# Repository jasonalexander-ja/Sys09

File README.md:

# Sys09 

Contains respositories for code and schematics/PCB layouts for the Sys09 6809 based computer.

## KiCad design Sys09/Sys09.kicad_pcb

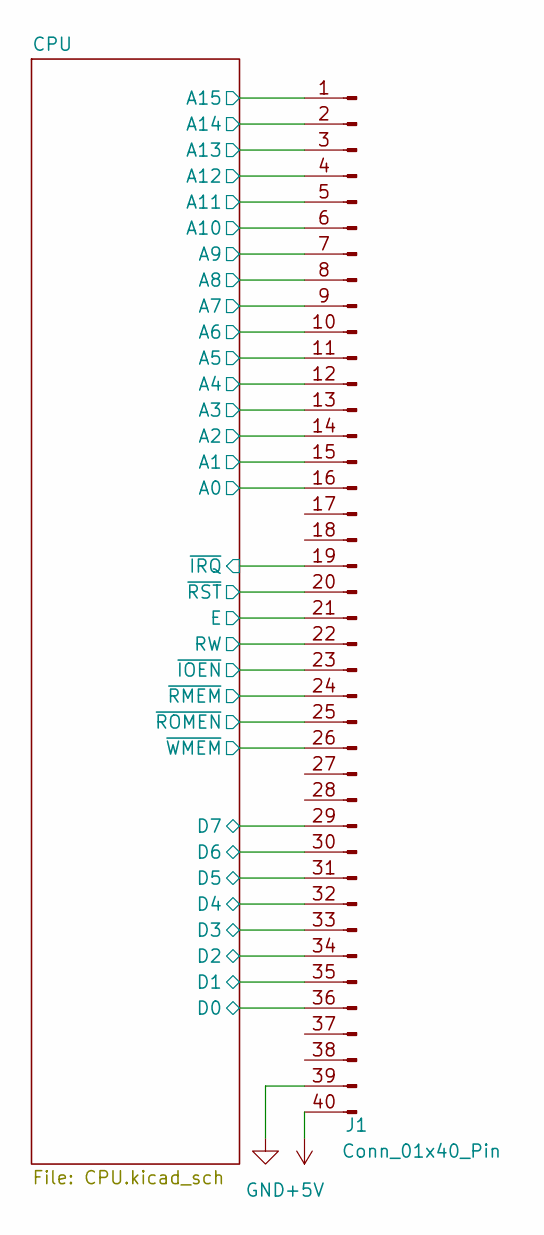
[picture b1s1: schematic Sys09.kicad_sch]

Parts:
J1: Conn_01x40_Pin; PinHeader_1x40_P2.54mm_Vertical

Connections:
+5V: J1.40; also elsewhere on the board
/CPU/A0: J1.16; also elsewhere on the board
/CPU/A1: J1.15; also elsewhere on the board
/CPU/A2: J1.14; also elsewhere on the board
/CPU/A3: J1.13; also elsewhere on the board
/CPU/A4: J1.12; also elsewhere on the board
/CPU/A5: J1.11; also elsewhere on the board
/CPU/A6: J1.10; also elsewhere on the board
/CPU/A7: J1.9; also elsewhere on the board
/CPU/A8: J1.8; also elsewhere on the board
/CPU/A9: J1.7; also elsewhere on the board
/CPU/A10: J1.6; also elsewhere on the board
/CPU/A11: J1.5; also elsewhere on the board
/CPU/A12: J1.4; also elsewhere on the board
/CPU/A13: J1.3; also elsewhere on the board
/CPU/A14: J1.2; also elsewhere on the board
/CPU/A15: J1.1; also elsewhere on the board
/CPU/D0: J1.36; also elsewhere on the board
/CPU/D1: J1.35; also elsewhere on the board
/CPU/D2: J1.34; also elsewhere on the board
/CPU/D3: J1.33; also elsewhere on the board
/CPU/D4: J1.32; also elsewhere on the board
/CPU/D5: J1.31; also elsewhere on the board
/CPU/D6: J1.30; also elsewhere on the board
/CPU/D7: J1.29; also elsewhere on the board
/CPU/E: J1.21; also elsewhere on the board
/CPU/RW: J1.22; also elsewhere on the board
/CPU/~IOEN: J1.23; also elsewhere on the board
/CPU/~IRQ: J1.19; also elsewhere on the board
/CPU/~RMEM: J1.24; also elsewhere on the board
/CPU/~ROMEN: J1.25; also elsewhere on the board
/CPU/~RST: J1.20; also elsewhere on the board
/CPU/~WMEM: J1.26; also elsewhere on the board
GND: J1.39; also elsewhere on the board

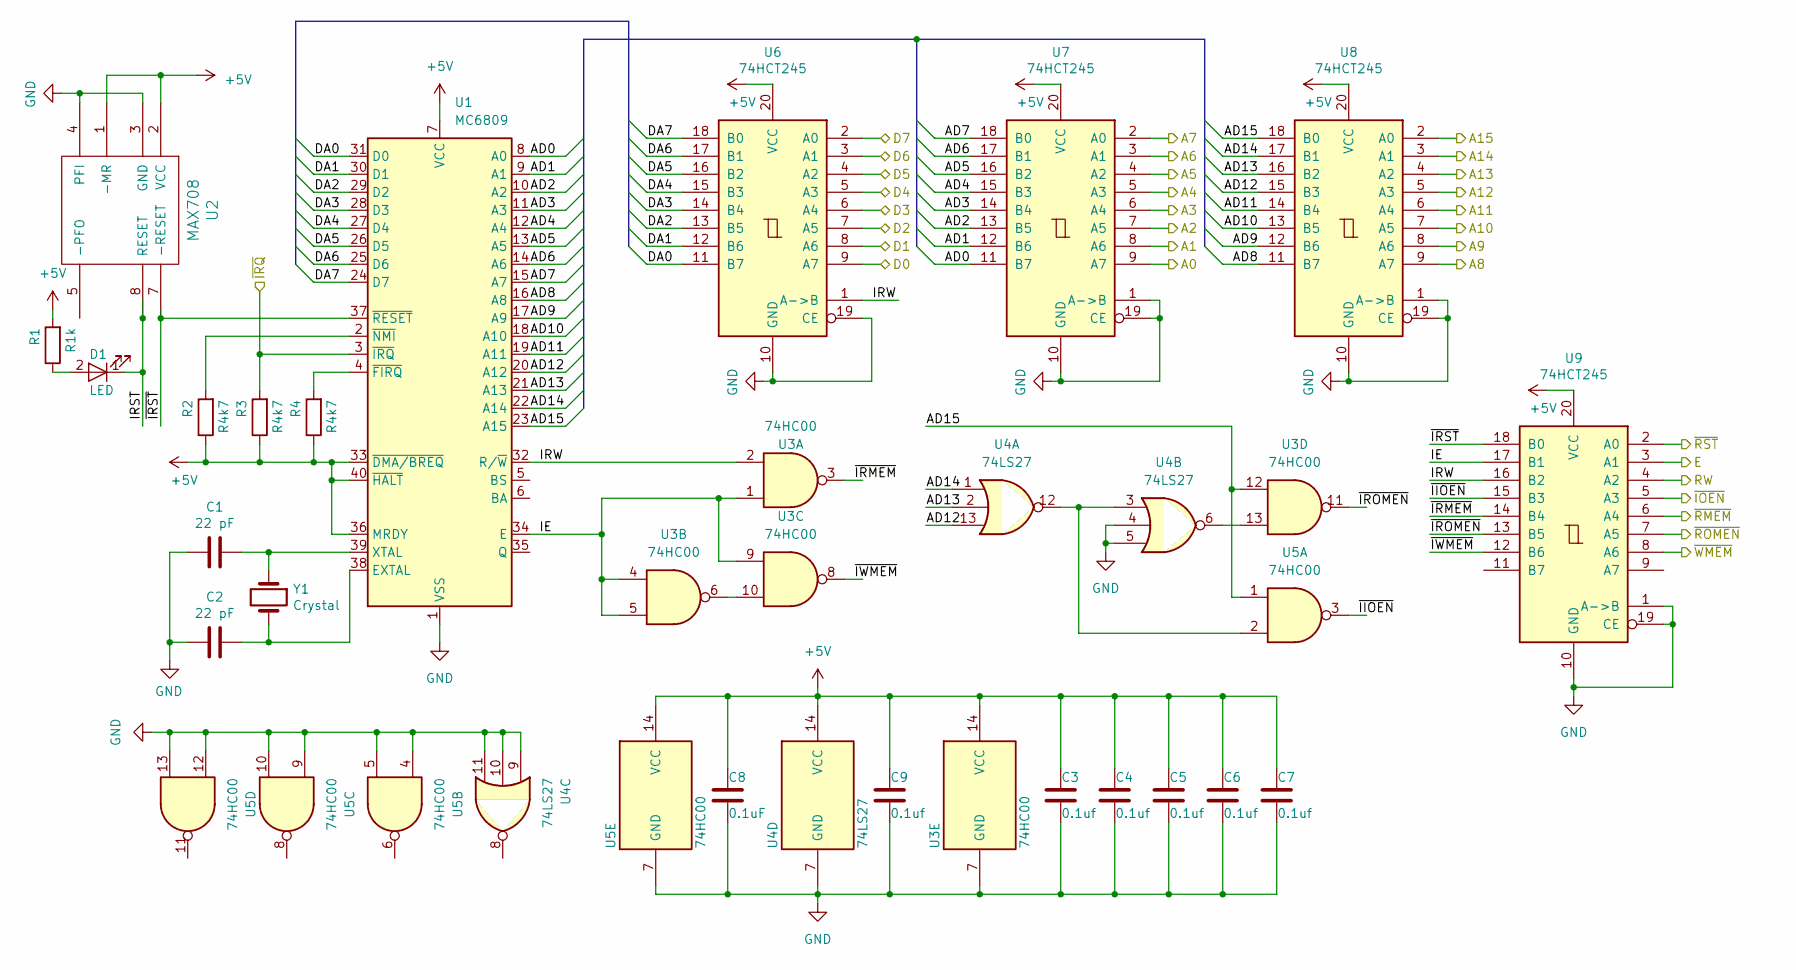
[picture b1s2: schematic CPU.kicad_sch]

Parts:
C1, C2: 22 pF; C_Disc_D5.0mm_W2.5mm_P2.50mm
C3, C4, C5, C6, C7, C9: 0.1uf; C_Disc_D5.0mm_W2.5mm_P2.50mm
C8: 0.1uF; C_Disc_D5.0mm_W2.5mm_P2.50mm
D1: LED; LED_D3.0mm
R1: R1k; R_Axial_DIN0207_L6.3mm_D2.5mm_P7.62mm_Horizontal
R2, R3, R4: R4k7; R_Axial_DIN0207_L6.3mm_D2.5mm_P7.62mm_Horizontal
U1: MC6809; DIP-40_W15.24mm
U2: MAX708; DIP-8_W7.62mm
U3, U5: 74HC00; DIP-14_W7.62mm
U4: 74LS27; DIP-14_W7.62mm
U6, U7, U8, U9: 74HCT245; DIP-20_W7.62mm
Y1: Crystal; Crystal_HC52-8mm_Vertical

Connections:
+5V: C3.1, C4.1, C5.1, C6.1, C7.1, C8.1, C9.1, R1.2, R2.1, R3.1, R4.1, U1.7 (VCC), U1.33 (~DMA/BREQ), U1.36 (MRDY), U1.40 (~HALT), U2.1 (-MR), U2.2 (VCC), U3.14 (VCC), U4.14 (VCC), U5.14 (VCC), U6.20 (VCC), U7.20 (VCC), U8.20 (VCC), U9.20 (VCC); also elsewhere on the board
/CPU/A0: U7.9 (A7); also elsewhere on the board
/CPU/A1: U7.8 (A6); also elsewhere on the board
/CPU/A2: U7.7 (A5); also elsewhere on the board
/CPU/A3: U7.6 (A4); also elsewhere on the board
/CPU/A4: U7.5 (A3); also elsewhere on the board
/CPU/A5: U7.4 (A2); also elsewhere on the board
/CPU/A6: U7.3 (A1); also elsewhere on the board
/CPU/A7: U7.2 (A0); also elsewhere on the board
/CPU/A8: U8.9 (A7); also elsewhere on the board
/CPU/A9: U8.8 (A6); also elsewhere on the board
/CPU/A10: U8.7 (A5); also elsewhere on the board
/CPU/A11: U8.6 (A4); also elsewhere on the board
/CPU/A12: U8.5 (A3); also elsewhere on the board
/CPU/A13: U8.4 (A2); also elsewhere on the board
/CPU/A14: U8.3 (A1); also elsewhere on the board
/CPU/A15: U8.2 (A0); also elsewhere on the board
/CPU/AD0: U1.8 (A0), U7.11 (B7)
/CPU/AD1: U1.9 (A1), U7.12 (B6)
/CPU/AD2: U1.10 (A2), U7.13 (B5)
/CPU/AD3: U1.11 (A3), U7.14 (B4)
/CPU/AD4: U1.12 (A4), U7.15 (B3)
/CPU/AD5: U1.13 (A5), U7.16 (B2)
/CPU/AD6: U1.14 (A6), U7.17 (B1)
/CPU/AD7: U1.15 (A7), U7.18 (B0)
/CPU/AD8: U1.16 (A8), U8.11 (B7)
/CPU/AD9: U1.17 (A9), U8.12 (B6)
/CPU/AD10: U1.18 (A10), U8.13 (B5)
/CPU/AD11: U1.19 (A11), U8.14 (B4)
/CPU/AD12: U1.20 (A12), U4.13, U8.15 (B3)
/CPU/AD13: U1.21 (A13), U4.2, U8.16 (B2)
/CPU/AD14: U1.22 (A14), U4.1, U8.17 (B1)
/CPU/AD15: U1.23 (A15), U3.12, U5.1, U8.18 (B0)
/CPU/D0: U6.9 (A7); also elsewhere on the board
/CPU/D1: U6.8 (A6); also elsewhere on the board
/CPU/D2: U6.7 (A5); also elsewhere on the board
/CPU/D3: U6.6 (A4); also elsewhere on the board
/CPU/D4: U6.5 (A3); also elsewhere on the board
/CPU/D5: U6.4 (A2); also elsewhere on the board
/CPU/D6: U6.3 (A1); also elsewhere on the board
/CPU/D7: U6.2 (A0); also elsewhere on the board
/CPU/DA0: U1.31 (D0), U6.11 (B7)
/CPU/DA1: U1.30 (D1), U6.12 (B6)
/CPU/DA2: U1.29 (D2), U6.13 (B5)
/CPU/DA3: U1.28 (D3), U6.14 (B4)
/CPU/DA4: U1.27 (D4), U6.15 (B3)
/CPU/DA5: U1.26 (D5), U6.16 (B2)
/CPU/DA6: U1.25 (D6), U6.17 (B1)
/CPU/DA7: U1.24 (D7), U6.18 (B0)
/CPU/E: U9.3 (A1); also elsewhere on the board
/CPU/IE: U1.34 (E), U3.1, U3.4, U3.5, U3.9, U9.17 (B1)
/CPU/IRST: D1.1 (K), U2.8 (RESET)
/CPU/IRW: U1.32 (R/~W), U3.2, U6.1 (A->B), U9.16 (B2)
/CPU/RW: U9.4 (A2); also elsewhere on the board
/CPU/~IIOEN: U5.3, U9.15 (B3)
/CPU/~IOEN: U9.5 (A3); also elsewhere on the board
/CPU/~IRMEM: U3.3, U9.14 (B4)
/CPU/~IROMEN: U3.11, U9.13 (B5)
/CPU/~IRQ: R3.2, U1.3 (~IRQ); also elsewhere on the board
/CPU/~IRST: U1.37 (~RESET), U2.7 (-RESET), U9.18 (B0)
/CPU/~IWMEM: U3.8, U9.12 (B6)
/CPU/~RMEM: U9.6 (A4); also elsewhere on the board
/CPU/~ROMEN: U9.7 (A5); also elsewhere on the board
/CPU/~RST: U9.2 (A0); also elsewhere on the board
/CPU/~WMEM: U9.8 (A6); also elsewhere on the board
GND: C1.1, C2.1, C3.2, C4.2, C5.2, C6.2, C7.2, C8.2, C9.2, U1.1 (VSS), U2.3 (GND), U2.4 (PFI), U3.7 (GND), U4.4, U4.5, U4.7 (GND), U4.9, U4.10, U4.11, U5.4, U5.5, U5.7 (GND), U5.9, U5.10, U5.12, U5.13, U6.10 (GND), U6.19 (CE), U7.1 (A->B), U7.10 (GND), U7.19 (CE), U8.1 (A->B), U8.10 (GND), U8.19 (CE), U9.1 (A->B), U9.10 (GND), U9.19 (CE); also elsewhere on the board
unnamed: D1.2 (A), R1.1
unnamed: C2.2, U1.38 (EXTAL), Y1.2
unnamed: C1.2, U1.39 (XTAL), Y1.1
unnamed: R4.2, U1.4 (~FIRQ)
unnamed: R2.2, U1.2 (~NMI)
unnamed: U3.6, U3.10
unnamed: U3.13, U4.6
unnamed: U4.3, U4.12, U5.2

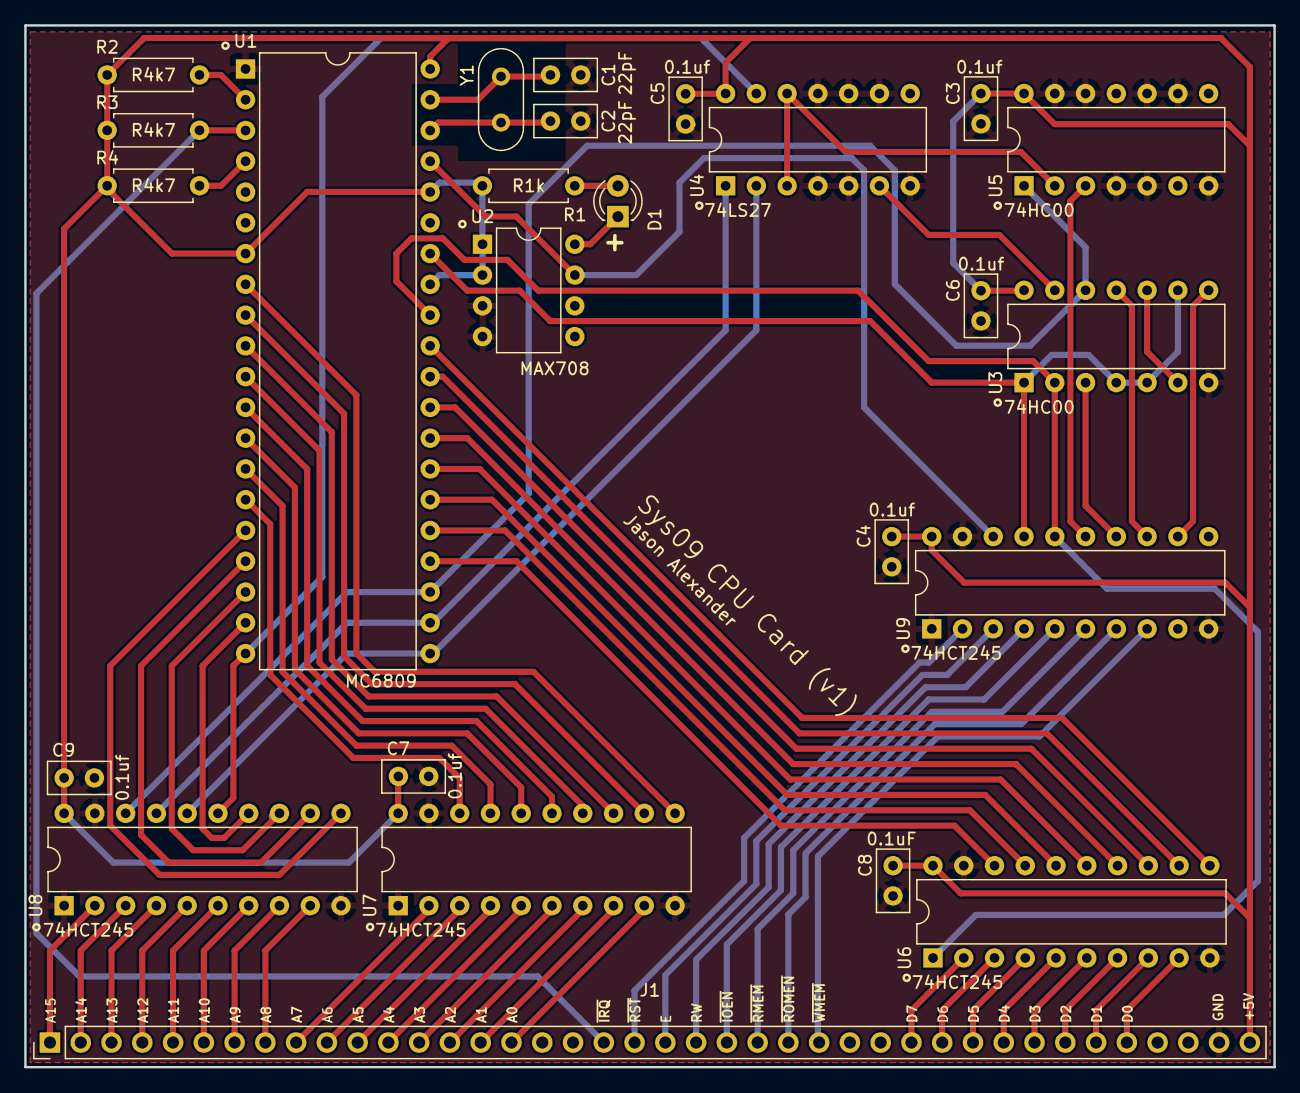
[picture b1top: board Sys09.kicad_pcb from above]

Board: 2 copper layers, 103.1 x 86.0 mm, 25 parts (0 on the bottom side), 74 nets.

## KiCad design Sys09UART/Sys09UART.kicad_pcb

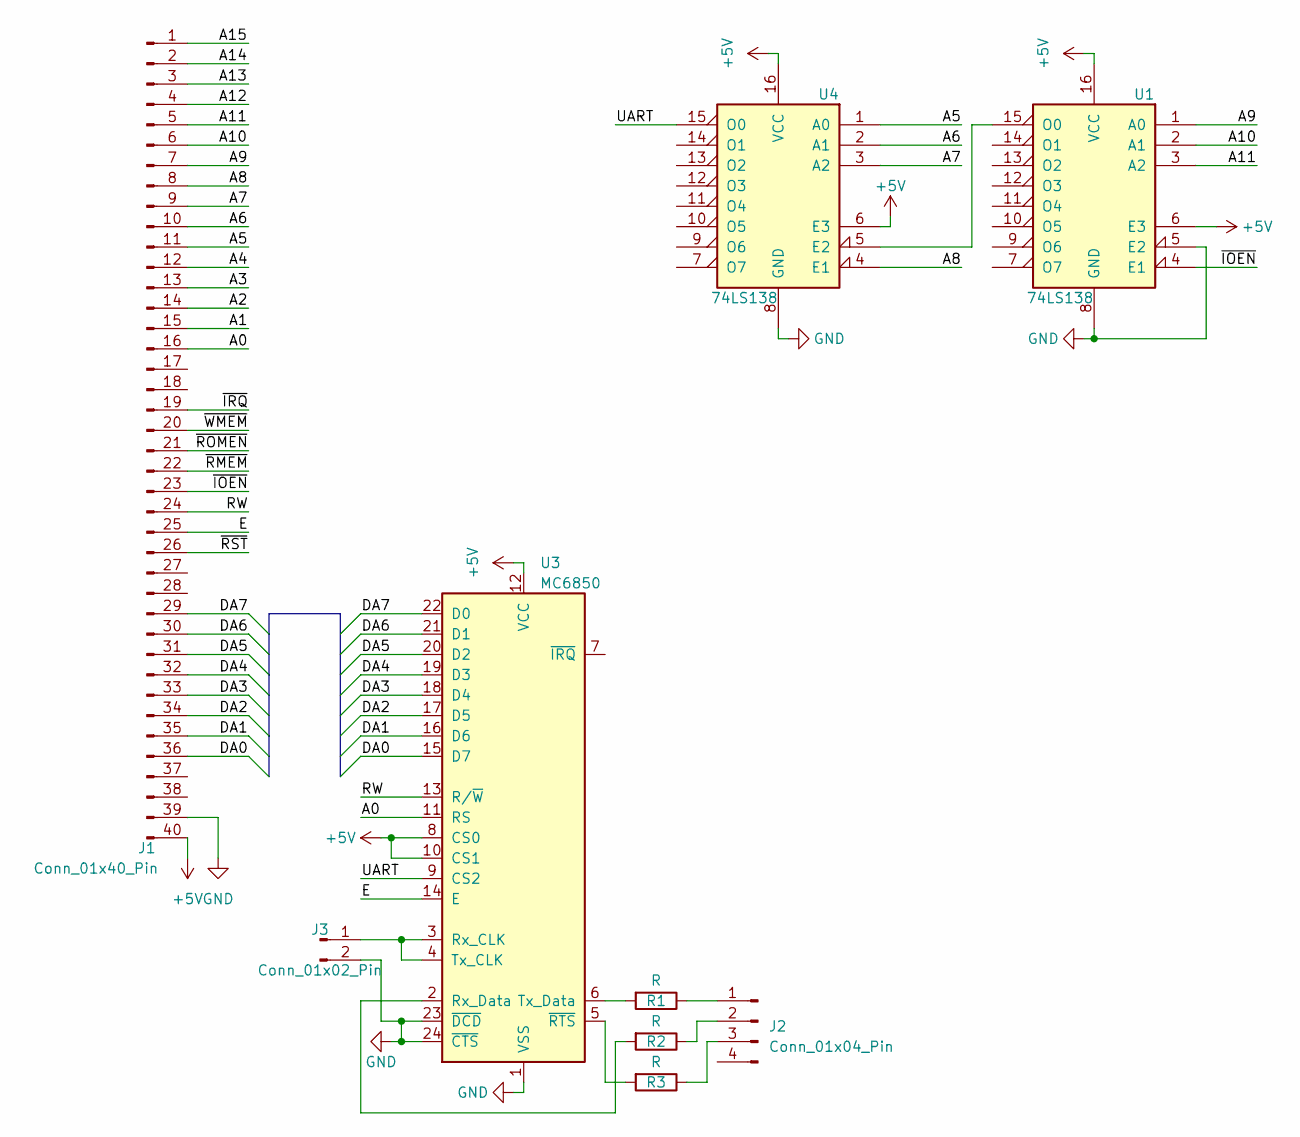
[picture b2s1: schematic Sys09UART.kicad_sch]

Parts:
J1: Conn_01x40_Pin; PinHeader_1x40_P2.54mm_Vertical
J2: Conn_01x04_Pin; PinHeader_1x04_P2.54mm_Vertical
J3: Conn_01x02_Pin; PinHeader_1x02_P2.54mm_Vertical
R1, R2, R3: R; R_Axial_DIN0207_L6.3mm_D2.5mm_P7.62mm_Horizontal
U1, U4: 74LS138; DIP-16_W7.62mm
U3: MC6850; DIP-24_W15.24mm

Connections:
+5V: J1.40, U1.6 (E3), U1.16 (VCC), U3.8 (CS0), U3.10 (CS1), U3.12 (VCC), U4.6 (E3), U4.16 (VCC)
/A0: J1.16, U3.11 (RS)
/A1: J1.15
/A2: J1.14
/A3: J1.13
/A4: J1.12
/A5: J1.11, U4.1 (A0)
/A6: J1.10, U4.2 (A1)
/A7: J1.9, U4.3 (A2)
/A8: J1.8, U4.4 (E1)
/A9: J1.7, U1.1 (A0)
/A10: J1.6, U1.2 (A1)
/A11: J1.5, U1.3 (A2)
/A12: J1.4
/A13: J1.3
/A14: J1.2
/A15: J1.1
/DA0: J1.36, U3.15 (D7)
/DA1: J1.35, U3.16 (D6)
/DA2: J1.34, U3.17 (D5)
/DA3: J1.33, U3.18 (D4)
/DA4: J1.32, U3.19 (D3)
/DA5: J1.31, U3.20 (D2)
/DA6: J1.30, U3.21 (D1)
/DA7: J1.29, U3.22 (D0)
/E: J1.25, U3.14 (E)
/RW: J1.24, U3.13 (R/~W)
/UART: U3.9 (CS2), U4.15 (O0)
/~IOEN: J1.23, U1.4 (E1)
/~IRQ: J1.19
/~RMEM: J1.22
/~ROMEN: J1.21
/~RST: J1.26
/~WMEM: J1.20
GND: J1.39, J3.2, U1.5 (E2), U1.8 (GND), U3.1 (VSS), U3.23 (~DCD), U3.24 (~CTS), U4.8 (GND)
unnamed: J2.1, R1.1
unnamed: J2.2, R2.1
unnamed: J2.3, R3.1
unnamed: J3.1, U3.3 (Rx_CLK), U3.4 (Tx_CLK)
unnamed: U1.15 (O0), U4.5 (E2)
unnamed: R2.2, U3.2 (Rx_Data)
unnamed: R1.2, U3.6 (Tx_Data)
unnamed: R3.2, U3.5 (~RTS)

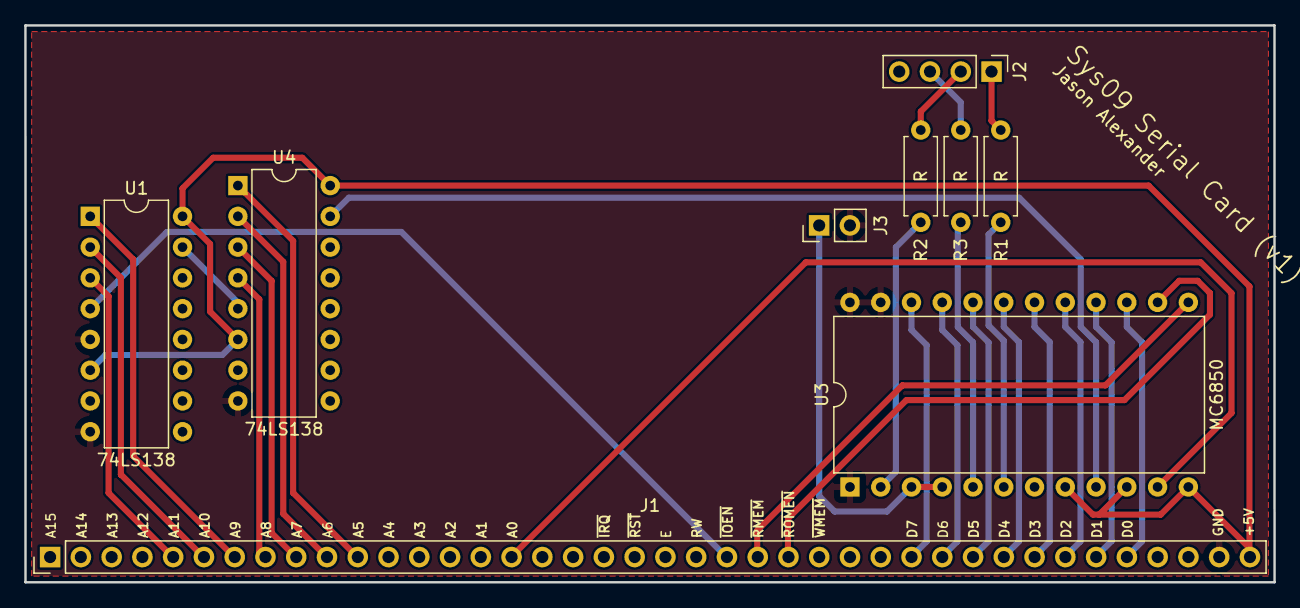
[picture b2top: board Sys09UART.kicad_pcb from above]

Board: 2 copper layers, 103.1 x 46.0 mm, 9 parts (0 on the bottom side), 30 nets.

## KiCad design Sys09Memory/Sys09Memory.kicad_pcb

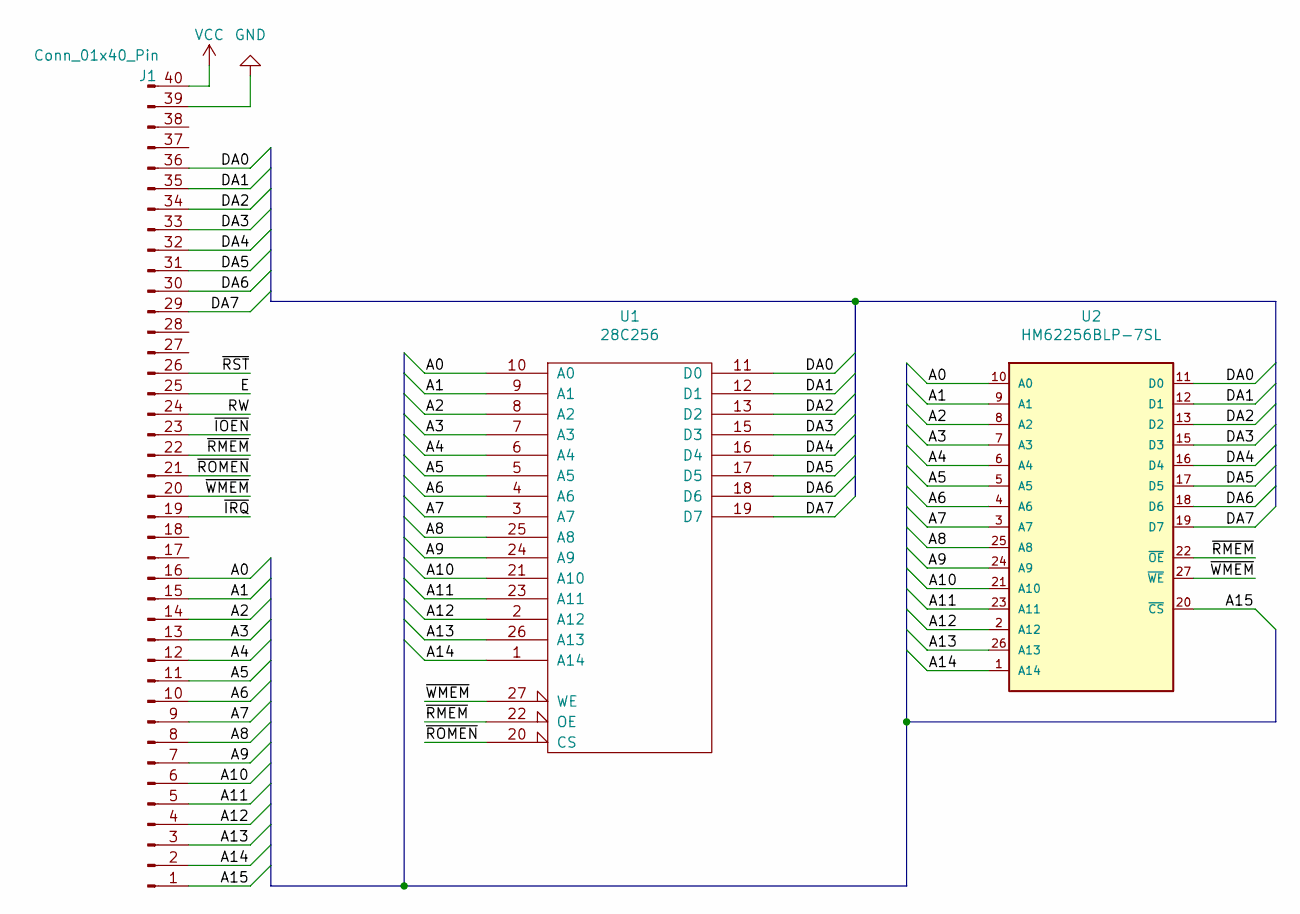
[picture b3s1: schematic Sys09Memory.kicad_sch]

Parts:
J1: Conn_01x40_Pin; PinHeader_1x40_P2.54mm_Vertical
U1: 28C256; DIP-28_W15.24mm
U2: HM62256BLP-7SL; DIP-28_W15.24mm

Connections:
/A0: J1.16, U1.10 (A0), U2.10 (A0)
/A1: J1.15, U1.9 (A1), U2.9 (A1)
/A2: J1.14, U1.8 (A2), U2.8 (A2)
/A3: J1.13, U1.7 (A3), U2.7 (A3)
/A4: J1.12, U1.6 (A4), U2.6 (A4)
/A5: J1.11, U1.5 (A5), U2.5 (A5)
/A6: J1.10, U1.4 (A6), U2.4 (A6)
/A7: J1.9, U1.3 (A7), U2.3 (A7)
/A8: J1.8, U1.25 (A8), U2.25 (A8)
/A9: J1.7, U1.24 (A9), U2.24 (A9)
/A10: J1.6, U1.21 (A10), U2.21 (A10)
/A11: J1.5, U1.23 (A11), U2.23 (A11)
/A12: J1.4, U1.2 (A12), U2.2 (A12)
/A13: J1.3, U1.26 (A13), U2.26 (A13)
/A14: J1.2, U1.1 (A14), U2.1 (A14)
/A15: J1.1, U2.20 (~CS)
/DA0: J1.36, U1.11 (D0), U2.11 (D0)
/DA1: J1.35, U1.12 (D1), U2.12 (D1)
/DA2: J1.34, U1.13 (D2), U2.13 (D2)
/DA3: J1.33, U1.15 (D3), U2.15 (D3)
/DA4: J1.32, U1.16 (D4), U2.16 (D4)
/DA5: J1.31, U1.17 (D5), U2.17 (D5)
/DA6: J1.30, U1.18 (D6), U2.18 (D6)
/DA7: J1.29, U1.19 (D7), U2.19 (D7)
/E: J1.25
/RW: J1.24
/~IOEN: J1.23
/~IRQ: J1.19
/~RMEM: J1.22, U1.22 (OE), U2.22 (~OE)
/~ROMEN: J1.21, U1.20 (CS)
/~RST: J1.26
/~WMEM: J1.20, U1.27 (WE), U2.27 (~WE)
GND: J1.39, U1.14 (GND), U2.14 (GND)
VCC: J1.40, U1.28 (VCC), U2.28 (VCC)

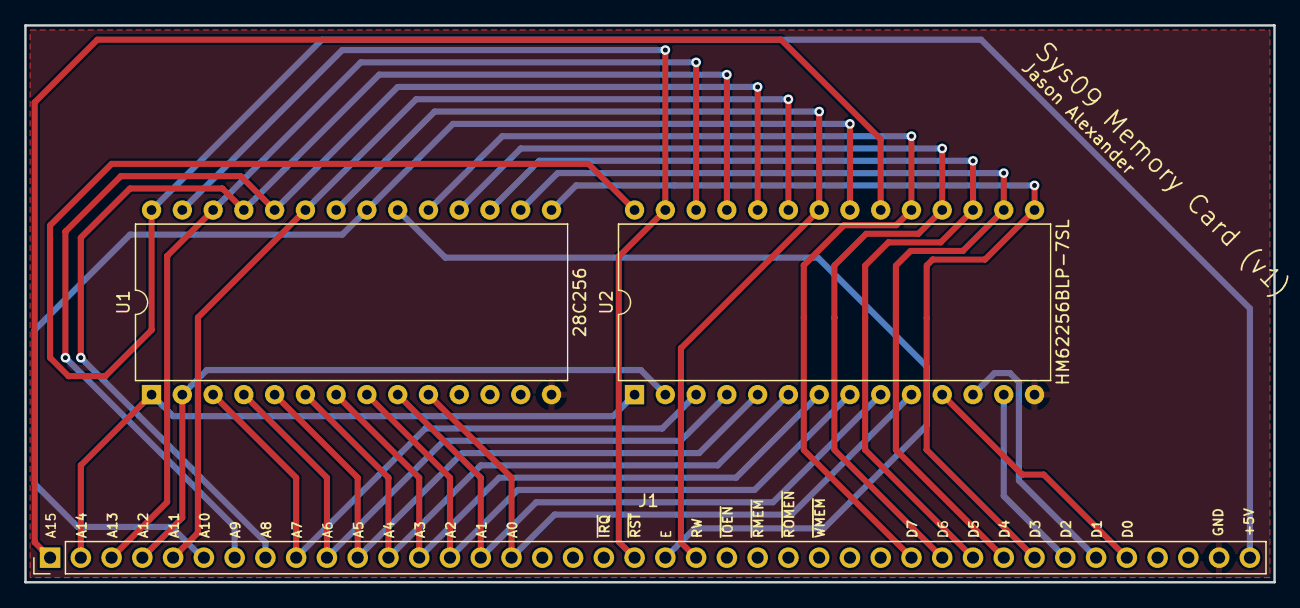
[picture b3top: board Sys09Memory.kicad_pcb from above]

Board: 2 copper layers, 103.1 x 46.0 mm, 3 parts (0 on the bottom side), 29 nets.

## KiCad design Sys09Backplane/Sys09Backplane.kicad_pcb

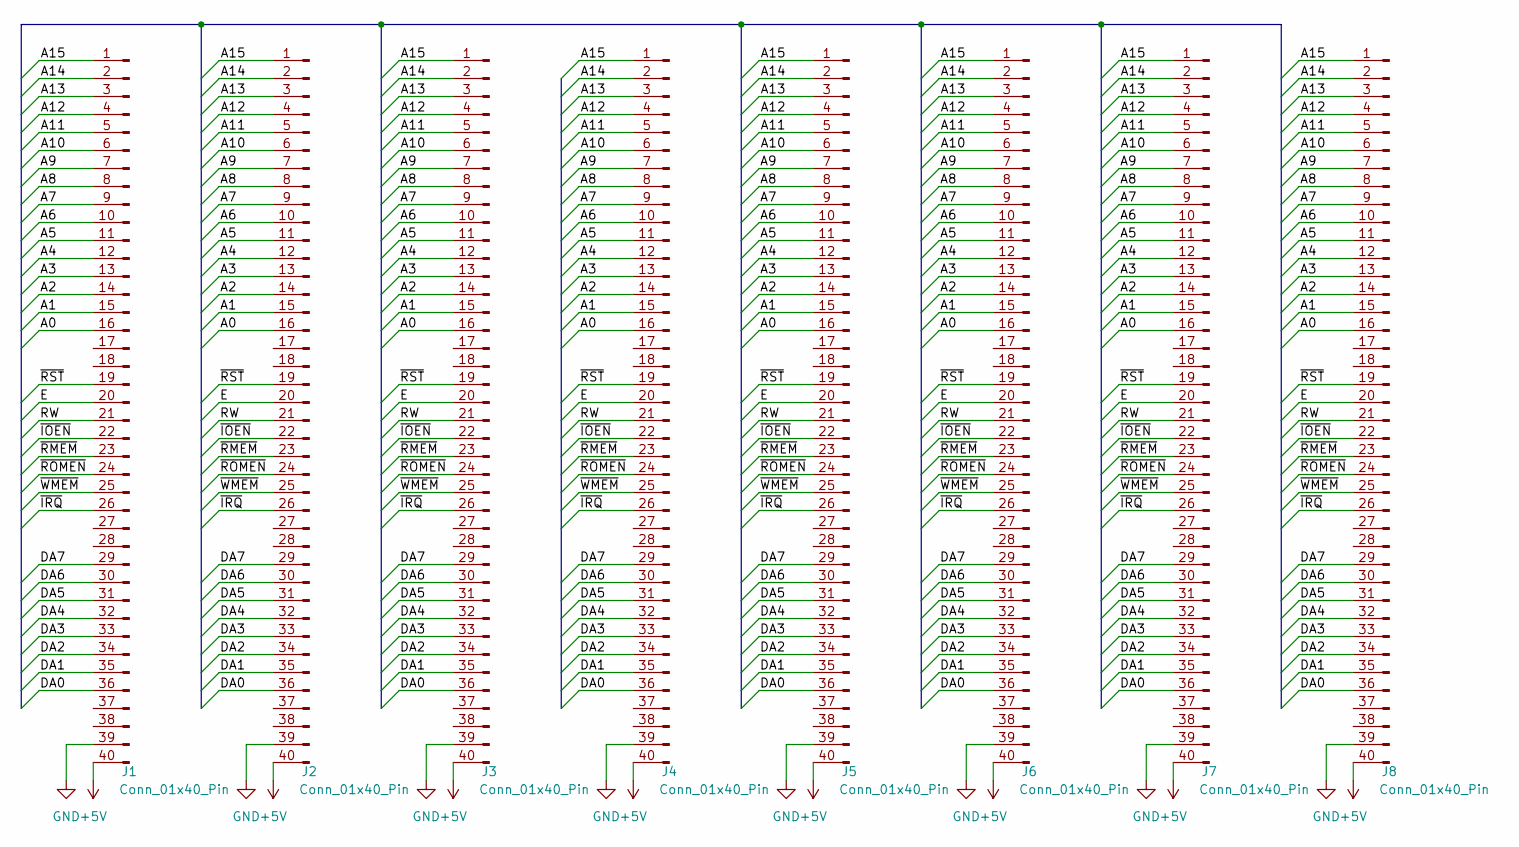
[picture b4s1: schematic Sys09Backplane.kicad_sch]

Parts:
J1, J2, J3, J4, J5, J6, J7, J8: Conn_01x40_Pin; PinHeader_1x40_P2.54mm_Vertical

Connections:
+5V: J1.40, J2.40, J3.40, J4.40, J5.40, J6.40, J7.40, J8.40
/A0: J1.16, J2.16, J3.16, J4.16, J5.16, J6.16, J7.16, J8.16
/A1: J1.15, J2.15, J3.15, J4.15, J5.15, J6.15, J7.15, J8.15
/A2: J1.14, J2.14, J3.14, J4.14, J5.14, J6.14, J7.14, J8.14
/A3: J1.13, J2.13, J3.13, J4.13, J5.13, J6.13, J7.13, J8.13
/A4: J1.12, J2.12, J3.12, J4.12, J5.12, J6.12, J7.12, J8.12
/A5: J1.11, J2.11, J3.11, J4.11, J5.11, J6.11, J7.11, J8.11
/A6: J1.10, J2.10, J3.10, J4.10, J5.10, J6.10, J7.10, J8.10
/A7: J1.9, J2.9, J3.9, J4.9, J5.9, J6.9, J7.9, J8.9
/A8: J1.8, J2.8, J3.8, J4.8, J5.8, J6.8, J7.8, J8.8
/A9: J1.7, J2.7, J3.7, J4.7, J5.7, J6.7, J7.7, J8.7
/A10: J1.6, J2.6, J3.6, J4.6, J5.6, J6.6, J7.6, J8.6
/A11: J1.5, J2.5, J3.5, J4.5, J5.5, J6.5, J7.5, J8.5
/A12: J1.4, J2.4, J3.4, J4.4, J5.4, J6.4, J7.4, J8.4
/A13: J1.3, J2.3, J3.3, J4.3, J5.3, J6.3, J7.3, J8.3
/A14: J1.2, J2.2, J3.2, J4.2, J5.2, J6.2, J7.2, J8.2
/A15: J1.1, J2.1, J3.1, J4.1, J5.1, J6.1, J7.1, J8.1
/DA0: J1.36, J2.36, J3.36, J4.36, J5.36, J6.36, J7.36, J8.36
/DA1: J1.35, J2.35, J3.35, J4.35, J5.35, J6.35, J7.35, J8.35
/DA2: J1.34, J2.34, J3.34, J4.34, J5.34, J6.34, J7.34, J8.34
/DA3: J1.33, J2.33, J3.33, J4.33, J5.33, J6.33, J7.33, J8.33
/DA4: J1.32, J2.32, J3.32, J4.32, J5.32, J6.32, J7.32, J8.32
/DA5: J1.31, J2.31, J3.31, J4.31, J5.31, J6.31, J7.31, J8.31
/DA6: J1.30, J2.30, J3.30, J4.30, J5.30, J6.30, J7.30, J8.30
/DA7: J1.29, J2.29, J3.29, J4.29, J5.29, J6.29, J7.29, J8.29
/E: J1.20, J2.20, J3.20, J4.20, J5.20, J6.20, J7.20, J8.20
/RW: J1.21, J2.21, J3.21, J4.21, J5.21, J6.21, J7.21, J8.21
/~IOEN: J1.22, J2.22, J3.22, J4.22, J5.22, J6.22, J7.22, J8.22
/~IRQ: J1.26, J2.26, J3.26, J4.26, J5.26, J6.26, J7.26, J8.26
/~RMEM: J1.23, J2.23, J3.23, J4.23, J5.23, J6.23, J7.23, J8.23
/~ROMEN: J1.24, J2.24, J3.24, J4.24, J5.24, J6.24, J7.24, J8.24
/~RST: J1.19, J2.19, J3.19, J4.19, J5.19, J6.19, J7.19, J8.19
/~WMEM: J1.25, J2.25, J3.25, J4.25, J5.25, J6.25, J7.25, J8.25
GND: J1.39, J2.39, J3.39, J4.39, J5.39, J6.39, J7.39, J8.39

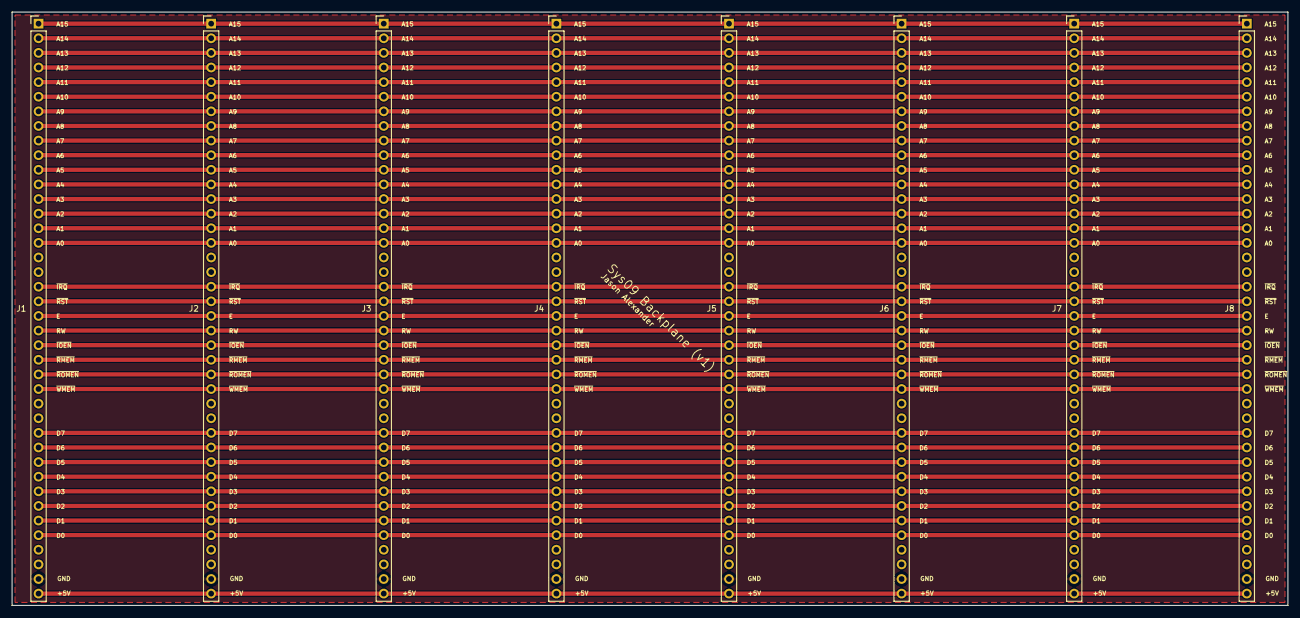
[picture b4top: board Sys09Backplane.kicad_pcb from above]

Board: 2 copper layers, 221.7 x 103.1 mm, 8 parts (0 on the bottom side), 34 nets.

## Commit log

2024-02-10 Added readme
2024-02-11 Added circuits for memory and serisl
